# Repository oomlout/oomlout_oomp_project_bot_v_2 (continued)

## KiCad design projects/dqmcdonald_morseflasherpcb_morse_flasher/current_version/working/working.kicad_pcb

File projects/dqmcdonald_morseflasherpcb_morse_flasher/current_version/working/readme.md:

# morseflasherpcb
 
## summary 
* id: dqmcdonald_morseflasherpcb_morse_flasher
* user: dqmcdonald
* name: morseflasherpcb
* board: morse_flasher
* repo: https://github.com/dqmcdonald/MorseFlasherPCB
* src_file_repo_kicad_pcb: Morse Flasher.kicad_pcb
* src_file_repo_kicad_pcb_link: https://github.com/dqmcdonald/MorseFlasherPCB/tree/master/Morse Flasher.kicad_pcb

* src_file_repo_sch: Morse Flasher.sch
* src_file_repo_sch_link: https://github.com/dqmcdonald/MorseFlasherPCB/tree/master/Morse Flasher.sch
* full details link: https://github.com/oomlout/oomlout_oomp_project_bot_v_2/tree/main/projects/dqmcdonald_morseflasherpcb_morse_flasher/current_version/working

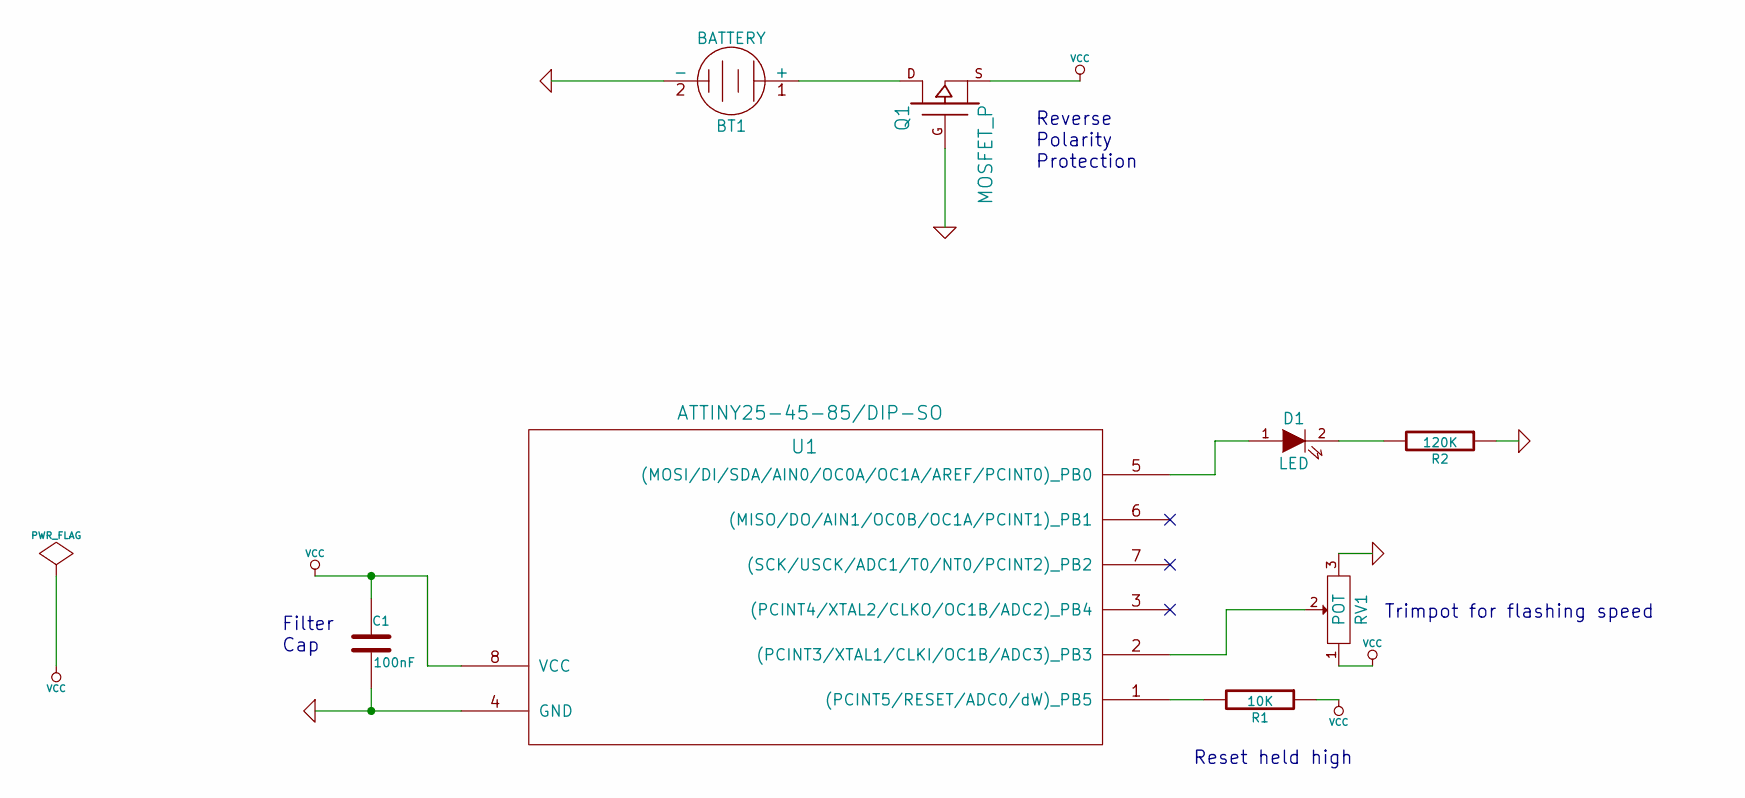
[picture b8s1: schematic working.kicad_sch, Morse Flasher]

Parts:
BT1: BATTERY
C1: 100nF
D1: LED
Q1: MOSFET_P
R1: 10K
R2: 120K
RV1: POT
U1: ATTINY25-45-85/DIP-SO

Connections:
GND: BT1.2 (-), C1.2, Q1.G, R2.1, RV1.3, U1.4 (GND)
unnamed: BT1.1 (+), Q1.D
unnamed: D1.1 (A), U1.5 ((MOSI/DI/SDA/AIN0/OC0A/OC1A/AREF/PCINT0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)
unnamed: D1.2 (K), R2.2
unnamed: R1.2, U1.1 ((PCINT5/RESET/ADC0/dW)_PB5)
unnamed: RV1.2, U1.2 ((PCINT3/XTAL1/CLKI/OC1B/ADC3)_PB3)
VCC: C1.1, Q1.S, R1.1, RV1.1, U1.8 (VCC)

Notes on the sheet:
Filter Cap
Reverse Polarity Protection
Trimpot for flashing speed
Reset held high

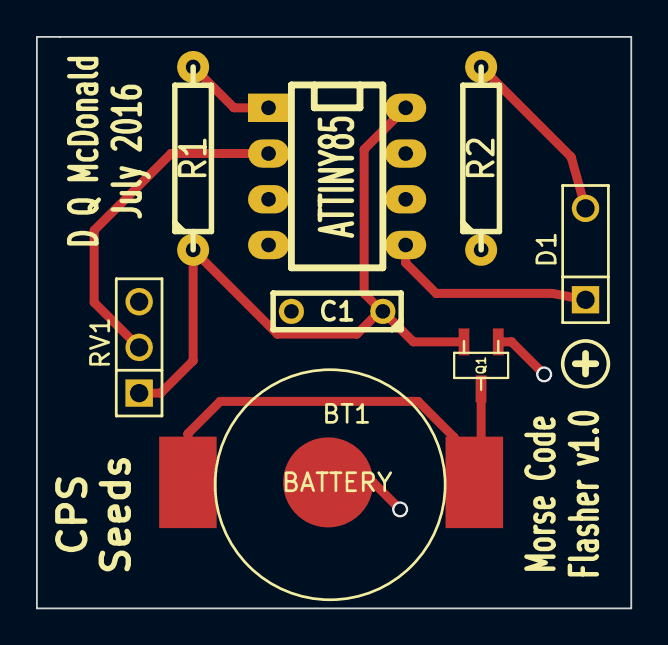
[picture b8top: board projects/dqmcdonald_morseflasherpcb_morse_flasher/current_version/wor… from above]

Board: 2 copper layers, 33.0 x 31.8 mm, 8 parts (0 on the bottom side), 7 nets.
